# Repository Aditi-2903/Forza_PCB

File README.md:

# Forza_PCB

https://www.youtube.com/watch?v=CCUaib22syc

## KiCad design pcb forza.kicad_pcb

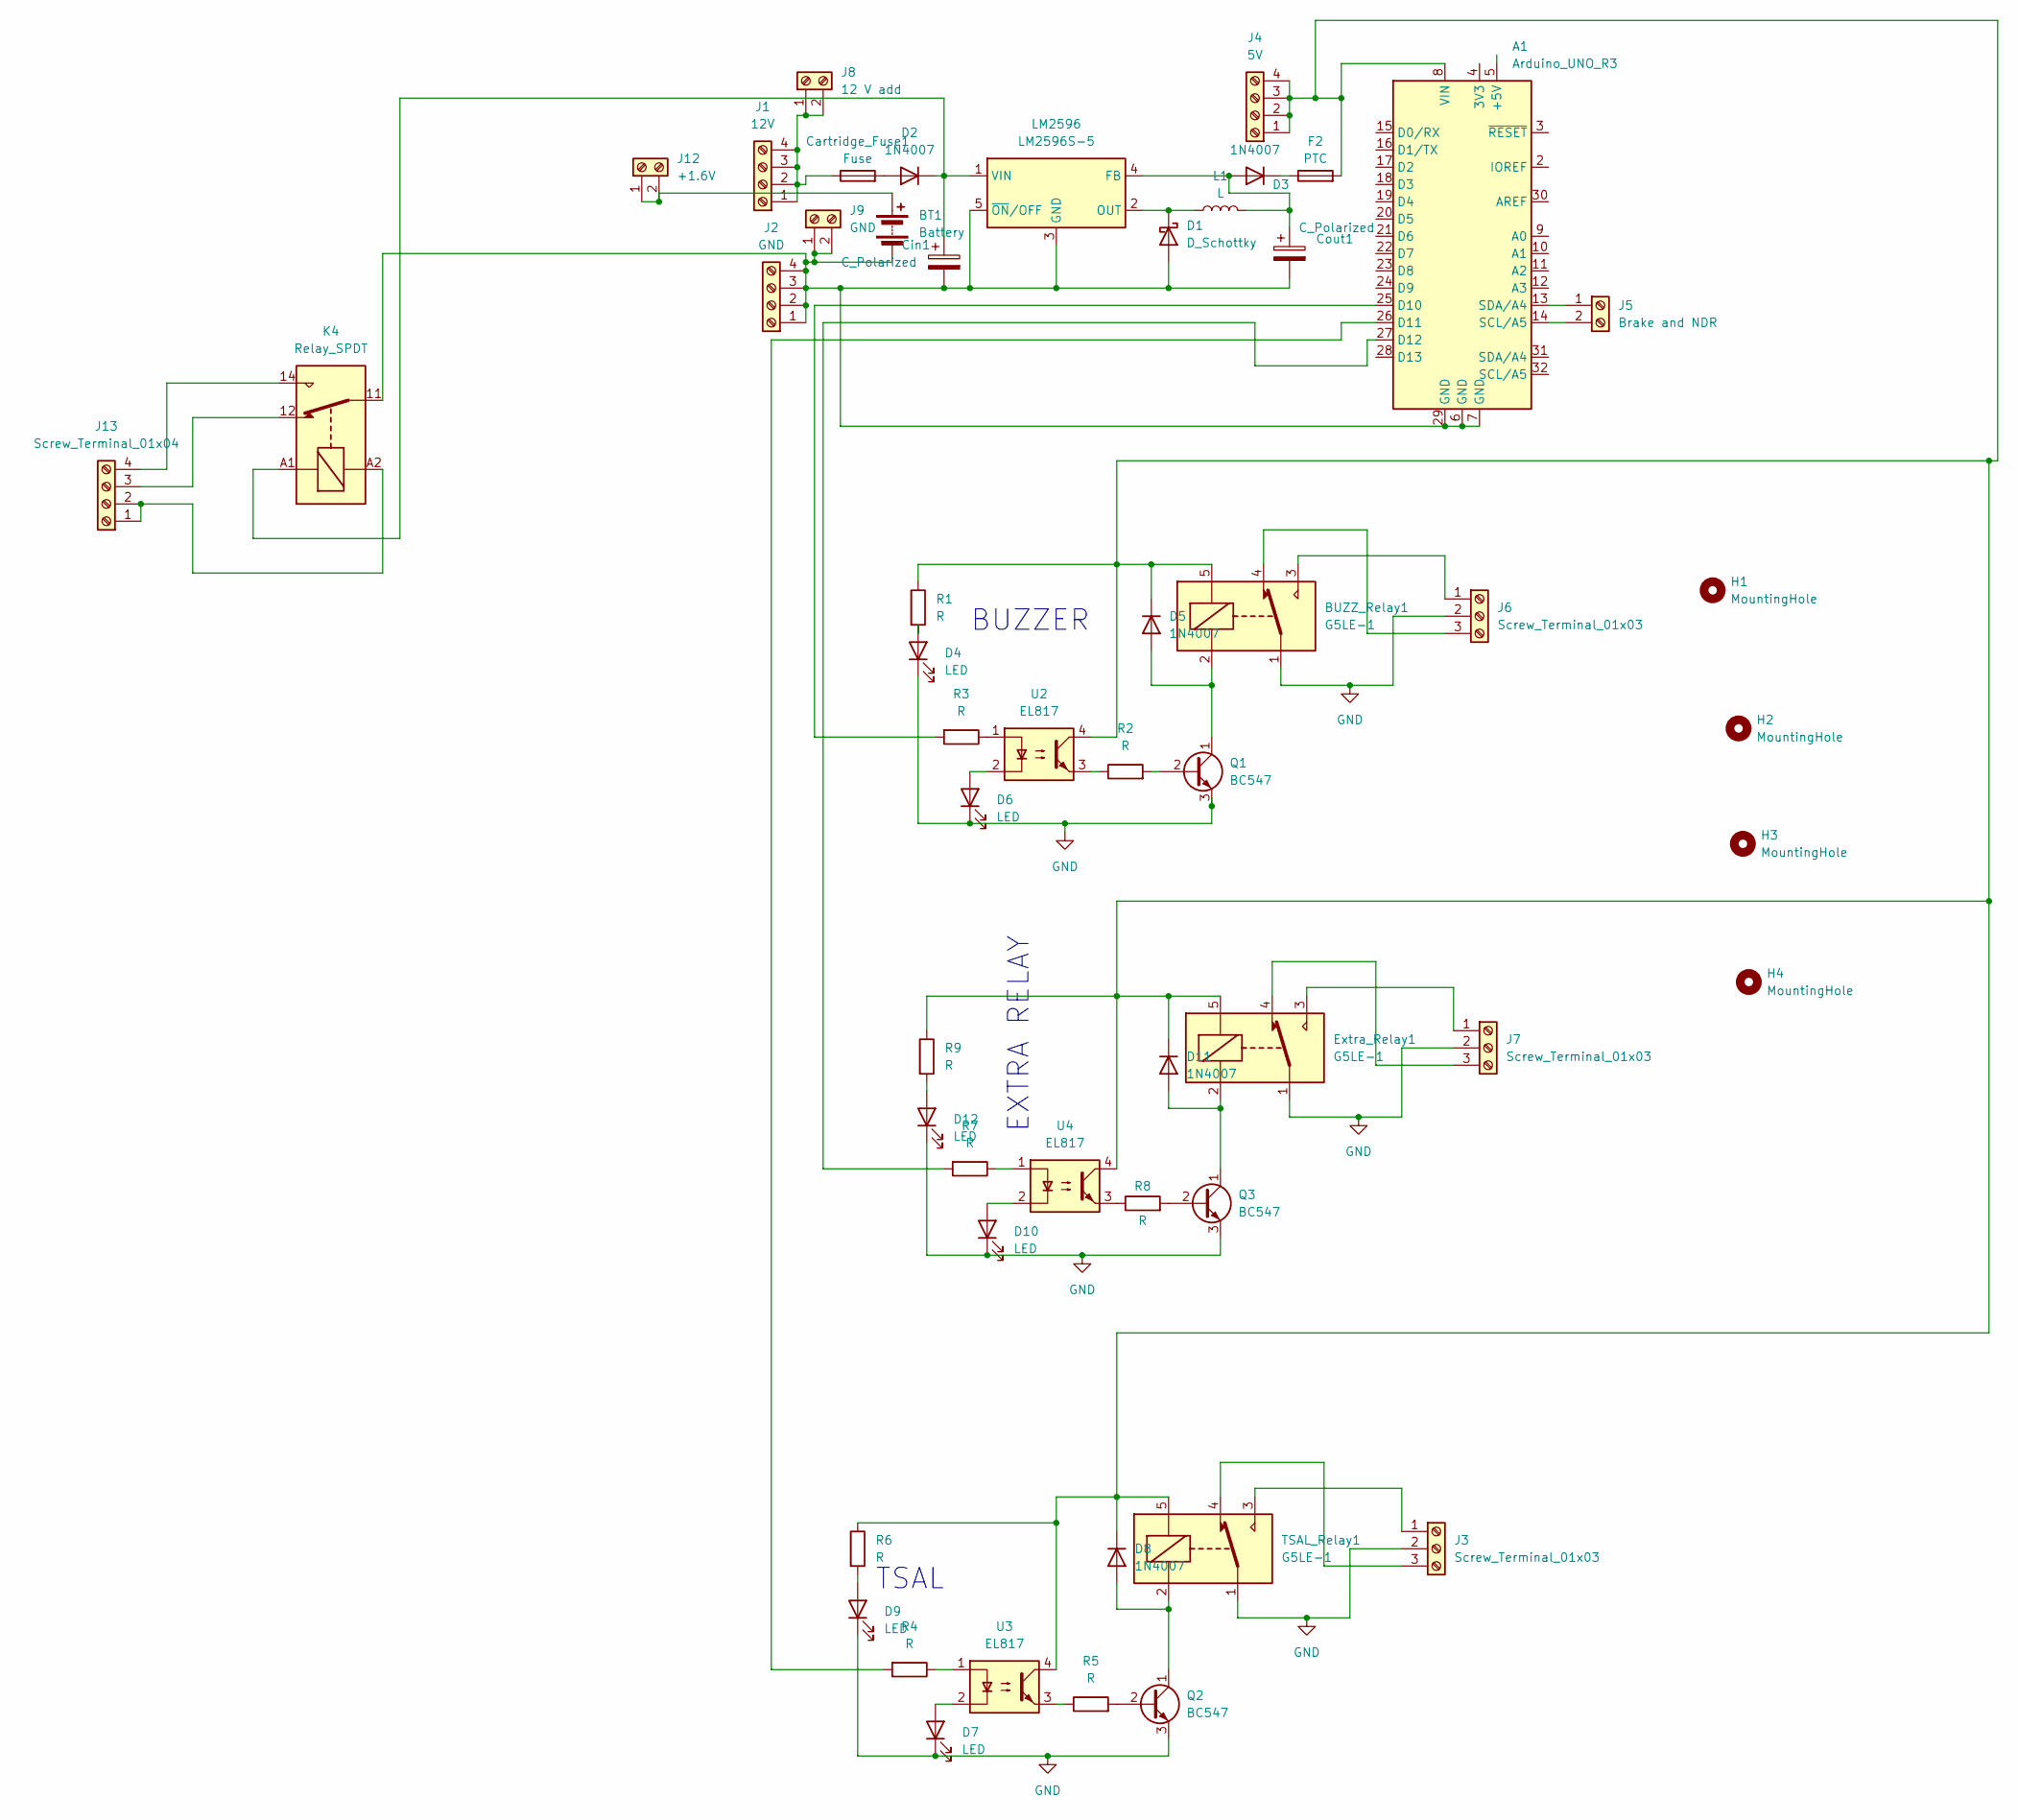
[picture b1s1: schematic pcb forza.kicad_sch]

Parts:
A1: Arduino_UNO_R3
BT1: Battery; BatteryHolder_Keystone_2462_2xAA
BUZZ_Relay1: G5LE-1; Relay_SPDT_Omron-G5LE-1
Cartridge_Fuse1: Fuse; Fuseholder_Cylinder-5x20mm_Schurter_0031_8201_Horizontal_Op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
Cin1: C_Polarized; CP_Elec_4x4.5
Cout1: C_Polarized; CP_Elec_4x4.5
D1: D_Schottky; D_SMF
D2, D3, D5, D8, D11: 1N4007; D_SOD-923
D4, D6, D7, D9, D10, D12: LED; LED_0402_1005Metric
Extra_Relay1: G5LE-1; Relay_SPDT_Omron-G5LE-1
F2: PTC; PTC FUSE
H1, H2, H3, H4: MountingHole; MountingHole_4.3mm_M4
J1: 12V; TerminalBlock_bornier-4_P5.08mm
J2: GND; TerminalBlock_bornier-4_P5.08mm
J3, J6, J7: Screw_Terminal_01x03; TerminalBlock_bornier-3_P5.08mm
J4: 5V; TerminalBlock_bornier-4_P5.08mm
J5: Brake and NDR; TerminalBlock_bornier-2_P5.08mm
J8: 12 V add; TerminalBlock_bornier-2_P5.08mm
J9: GND; TerminalBlock_bornier-2_P5.08mm
J12: +1.6V; TerminalBlock_bornier-2_P5.08mm
J13: Screw_Terminal_01x04; TerminalBlock_bornier-4_P5.08mm
K4: Relay_SPDT; LM91CS12VDC
L1: L; L_Bourns_SRR1260
LM2596: LM2596S-5; TO-263-5_TabPin3
Q1, Q2, Q3: BC547; TO-92_Inline
R1, R2, R3, R4, R5, R6, R7, R8, R9: R; R_0402_1005Metric_Pad0.72x0.64mm_HandSolder
TSAL_Relay1: G5LE-1; Relay_SPDT_Omron-G5LE-1
U2, U3, U4: EL817; DIP-4_W7.62mm_SMDSocket_SmallPads

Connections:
GND: BUZZ_Relay1.1, D4.1 (K), D6.1 (K), D7.1 (K), D9.1 (K), D10.1 (K), D12.1 (K), Extra_Relay1.1, J3.2, J6.2, J7.2, Q1.3 (E), Q2.3 (E), Q3.3 (E), TSAL_Relay1.1
unnamed: A1.25 (D10), R3.2
unnamed: A1.26 (D11), R4.2
unnamed: A1.27 (D12), R7.2
unnamed: A1.8 (VIN), BUZZ_Relay1.5, D5.1 (K), D8.1 (K), D11.1 (K), Extra_Relay1.5, F2.2, J4.1, J4.2, J4.3, J4.4, R1.1, R6.1, R9.1, TSAL_Relay1.5, U2.4, U3.4, U4.4
unnamed: BT1.1 (+), J12.1, J12.2
unnamed: A1.6 (GND), A1.7 (GND), A1.29 (GND), BT1.2 (-), Cin1.2, Cout1.2, D1.2 (A), J2.1, J2.2, J2.3, J2.4, J9.1, J9.2, K4.11, LM2596.3 (GND), LM2596.5 (~ON/OFF)
unnamed: D1.1 (K), L1.1, LM2596.2 (OUT)
unnamed: Cartridge_Fuse1.2, D2.2 (A)
unnamed: Cin1.1, D2.1 (K), K4.A1, LM2596.1 (VIN)
unnamed: Cout1.1, D3.2 (A), L1.2, LM2596.4 (FB)
unnamed: D3.1 (K), F2.1
unnamed: D4.2 (A), R1.2
unnamed: BUZZ_Relay1.2, D5.2 (A), Q1.1 (C)
unnamed: D6.2 (A), U2.2
unnamed: D7.2 (A), U3.2
unnamed: D8.2 (A), Q2.1 (C), TSAL_Relay1.2
unnamed: D9.2 (A), R6.2
unnamed: D10.2 (A), U4.2
unnamed: D11.2 (A), Extra_Relay1.2, Q3.1 (C)
unnamed: D12.2 (A), R9.2
unnamed: Cartridge_Fuse1.1, J1.1, J1.2, J1.3, J1.4, J8.1, J8.2
unnamed: J3.1, TSAL_Relay1.3
unnamed: J3.3, TSAL_Relay1.4
unnamed: A1.13 (SDA/A4), J5.1
unnamed: A1.14 (SCL/A5), J5.2
unnamed: BUZZ_Relay1.3, J6.1
unnamed: BUZZ_Relay1.4, J6.3
unnamed: Extra_Relay1.3, J7.1
unnamed: Extra_Relay1.4, J7.3
unnamed: J13.1, J13.2, K4.A2
unnamed: J13.3, K4.12
unnamed: J13.4, K4.14
unnamed: Q1.2 (B), R2.2
unnamed: Q2.2 (B), R5.2
unnamed: Q3.2 (B), R8.2
unnamed: R2.1, U2.3
unnamed: R3.1, U2.1
unnamed: R4.1, U3.1
unnamed: R5.1, U3.3
unnamed: R7.1, U4.1
unnamed: R8.1, U4.3

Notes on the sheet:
BUZZER
TSAL
EXTRA RELAY

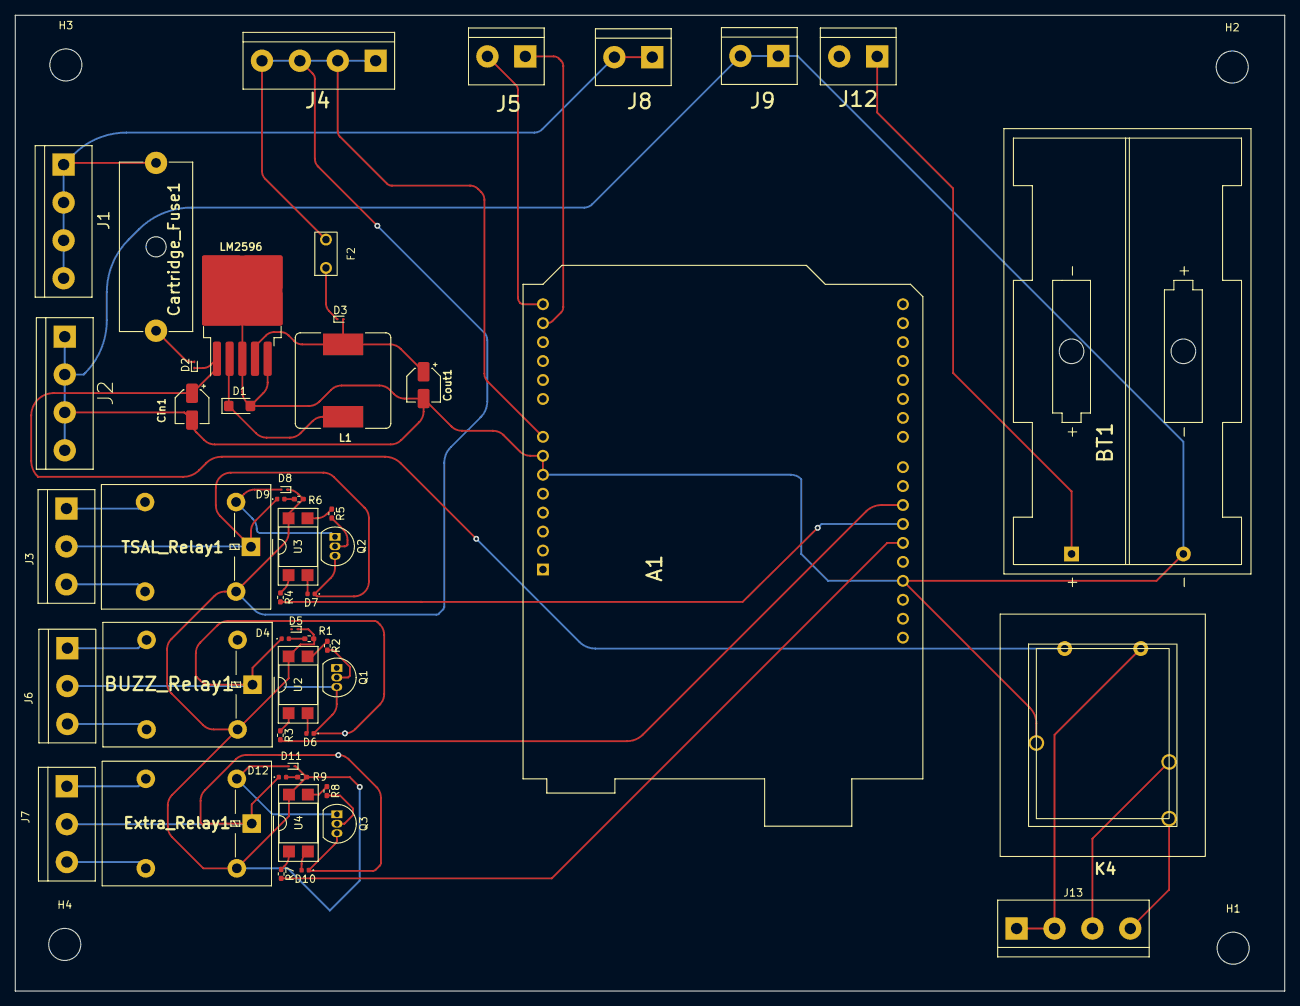
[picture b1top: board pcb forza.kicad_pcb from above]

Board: 2 copper layers, 170.2 x 130.8 mm, 54 parts (0 on the bottom side), 42 nets.
